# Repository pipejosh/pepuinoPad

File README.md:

# Pepuino Pad

This is the pepuino pad, a 9 by 9 midi launchpad, with per key rgb illumination (the brightness can only be set to 30% ish) the pepuino pad is a midi compatible launchpad to make music, this project, the shematics and the pcb are made in kicad, and the case and render are made in fusion 360 and it uses the custom made pepuino nano V1 as the main microcontroler (microcontroller based on a rp2040 chip)

###  Shematic
 
### pcb
 
### case
 
### render

## BOM

## Components (KIT)

| Item | Description | Quantity | Unit Price | Total Price | URL |
|-----|------------|----------|------------|-------------|-----|
| Blank keycaps | White | 90 | 0,13 | 11,81 | https://www.aliexpress.com/item/32842379355.html |
| Blank keycaps | Green | 20 | 0,19 | 3,77 | https://www.aliexpress.com/item/1005006116865547.html |
| Switches | Mechanical switches | 90 | 0,23 | 20,31 | https://www.aliexpress.com/item/1005009787231480.html |
| Diodes | SMD diodes | 100 | 0,03 | 3,08 | https://www.aliexpress.com/item/1005007160563285.html |
| M2 standoff | M2 standoff 5mm | 50 | 0,05 | 2,47 | https://www.aliexpress.com/item/1005006049595637.html |
| M2 screw | 5mm screw | 50 | 0,03 | 1,65 | https://www.aliexpress.com/item/1005005070119421.html |
| LED | SK6812 | 100 | 0,07 | 6,67 | https://www.aliexpress.com/item/1005005193716172.html |
| Roraty encoder | ec11 | 1 | 1,85 | 1,85 | https://www.aliexpress.com/item/1005007644083514.html |
| Taxes | AliExpress tax | — | — | 4,28 | — |

**Components Subtotal:** **55,89**

---

## PCB

| Item | Description | Price |
|-----|------------|-------|
| JLCPCB | Pepuino Pad PCB | 24,41 |
| JLCPCB Shipping | PCB shipping + taxes | 18,44 |

---

## Total

| Description | Amount |
|------------|--------|
| **Grand Total** | **98.74** |

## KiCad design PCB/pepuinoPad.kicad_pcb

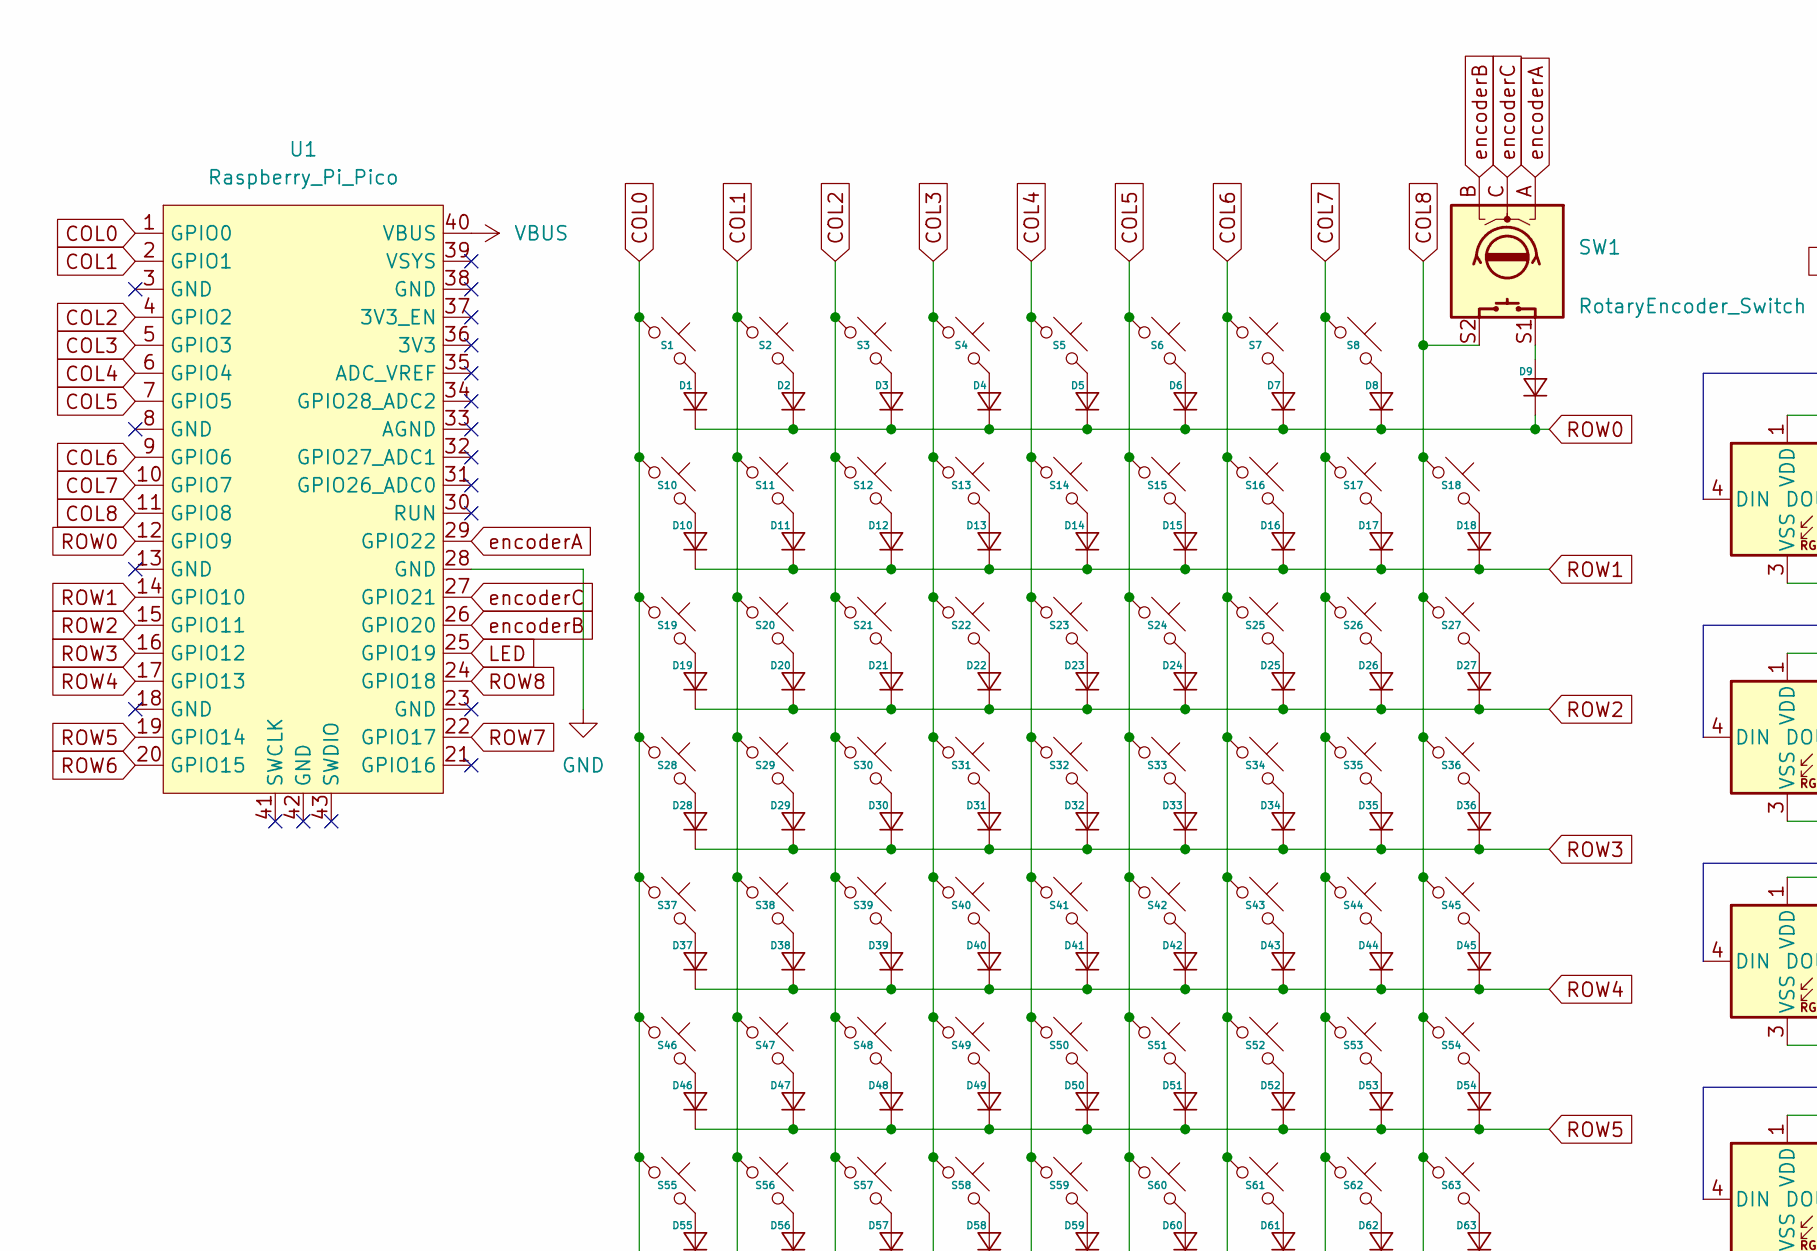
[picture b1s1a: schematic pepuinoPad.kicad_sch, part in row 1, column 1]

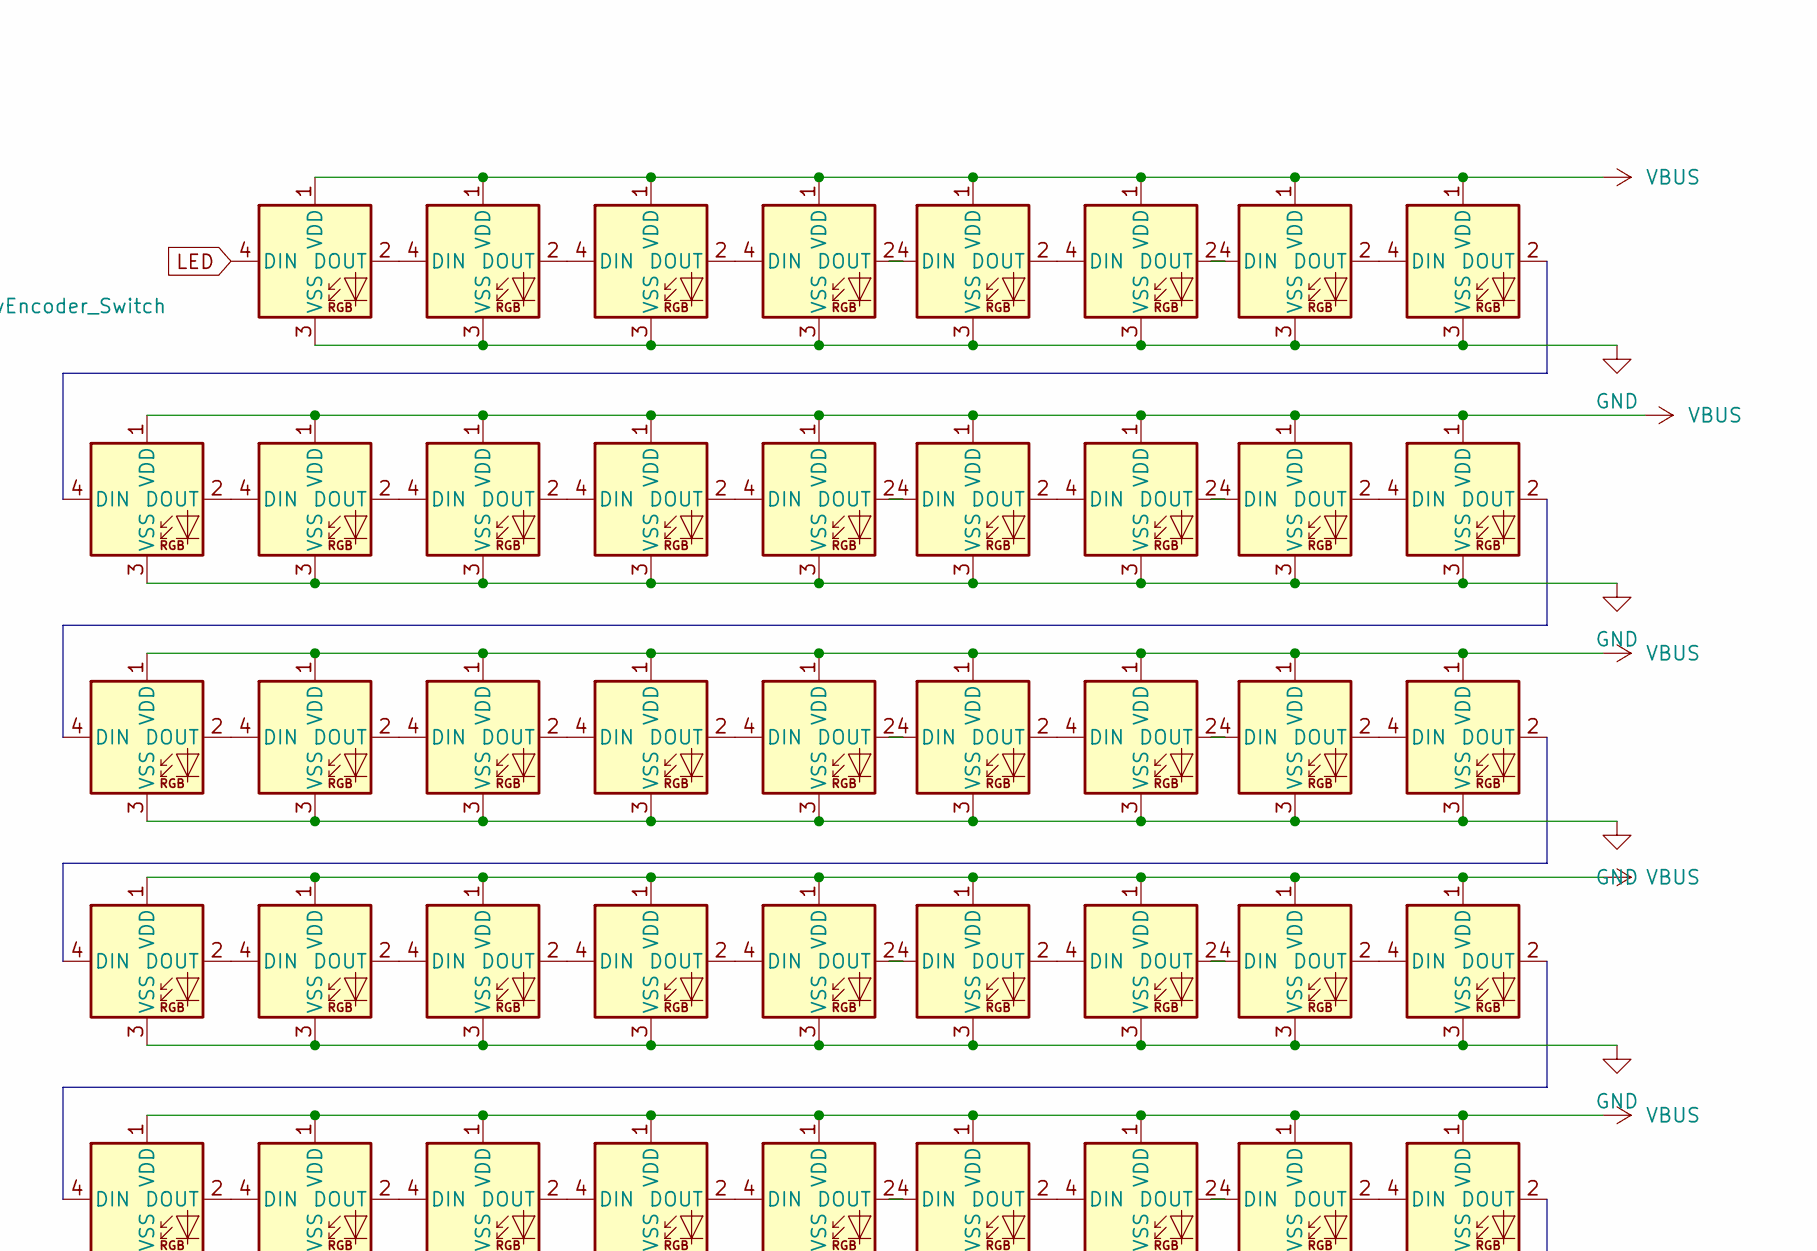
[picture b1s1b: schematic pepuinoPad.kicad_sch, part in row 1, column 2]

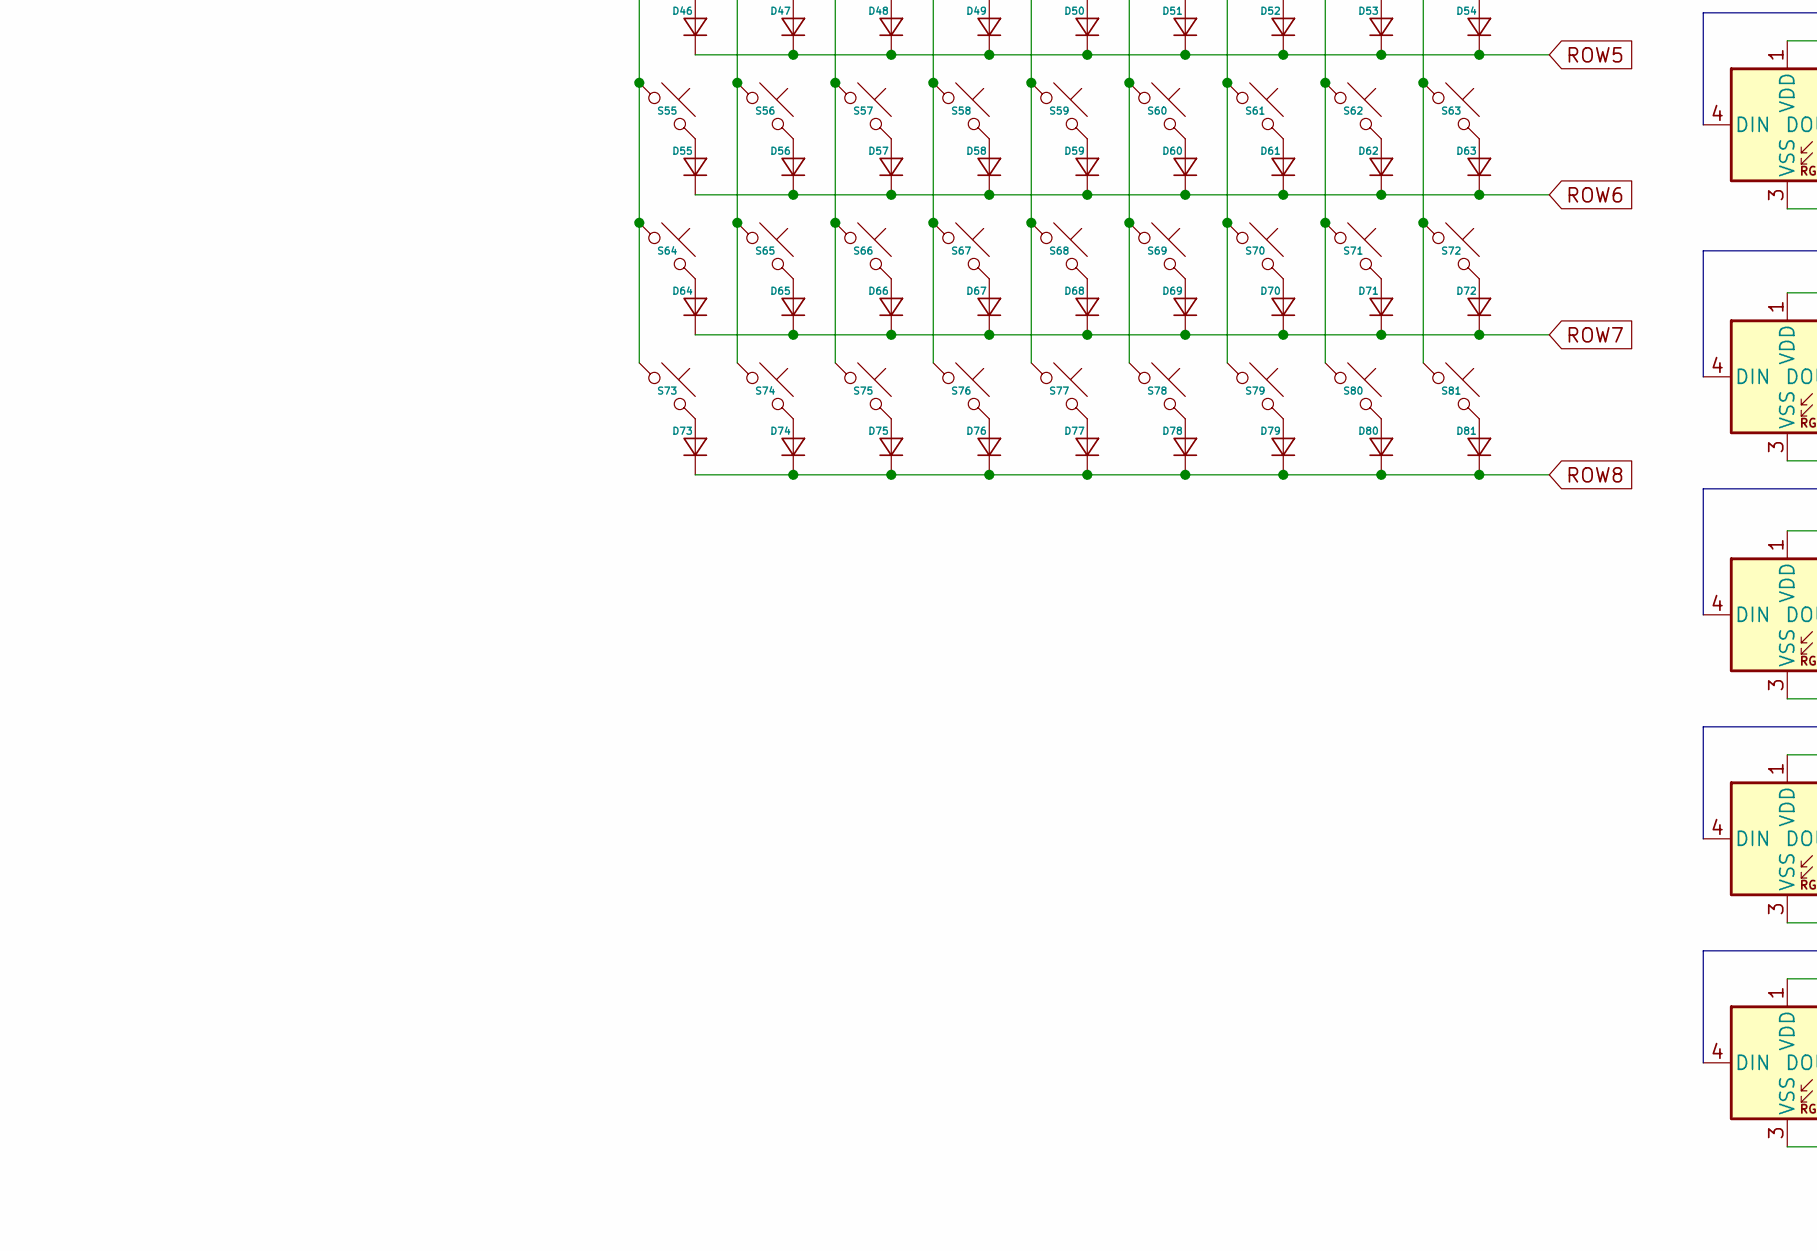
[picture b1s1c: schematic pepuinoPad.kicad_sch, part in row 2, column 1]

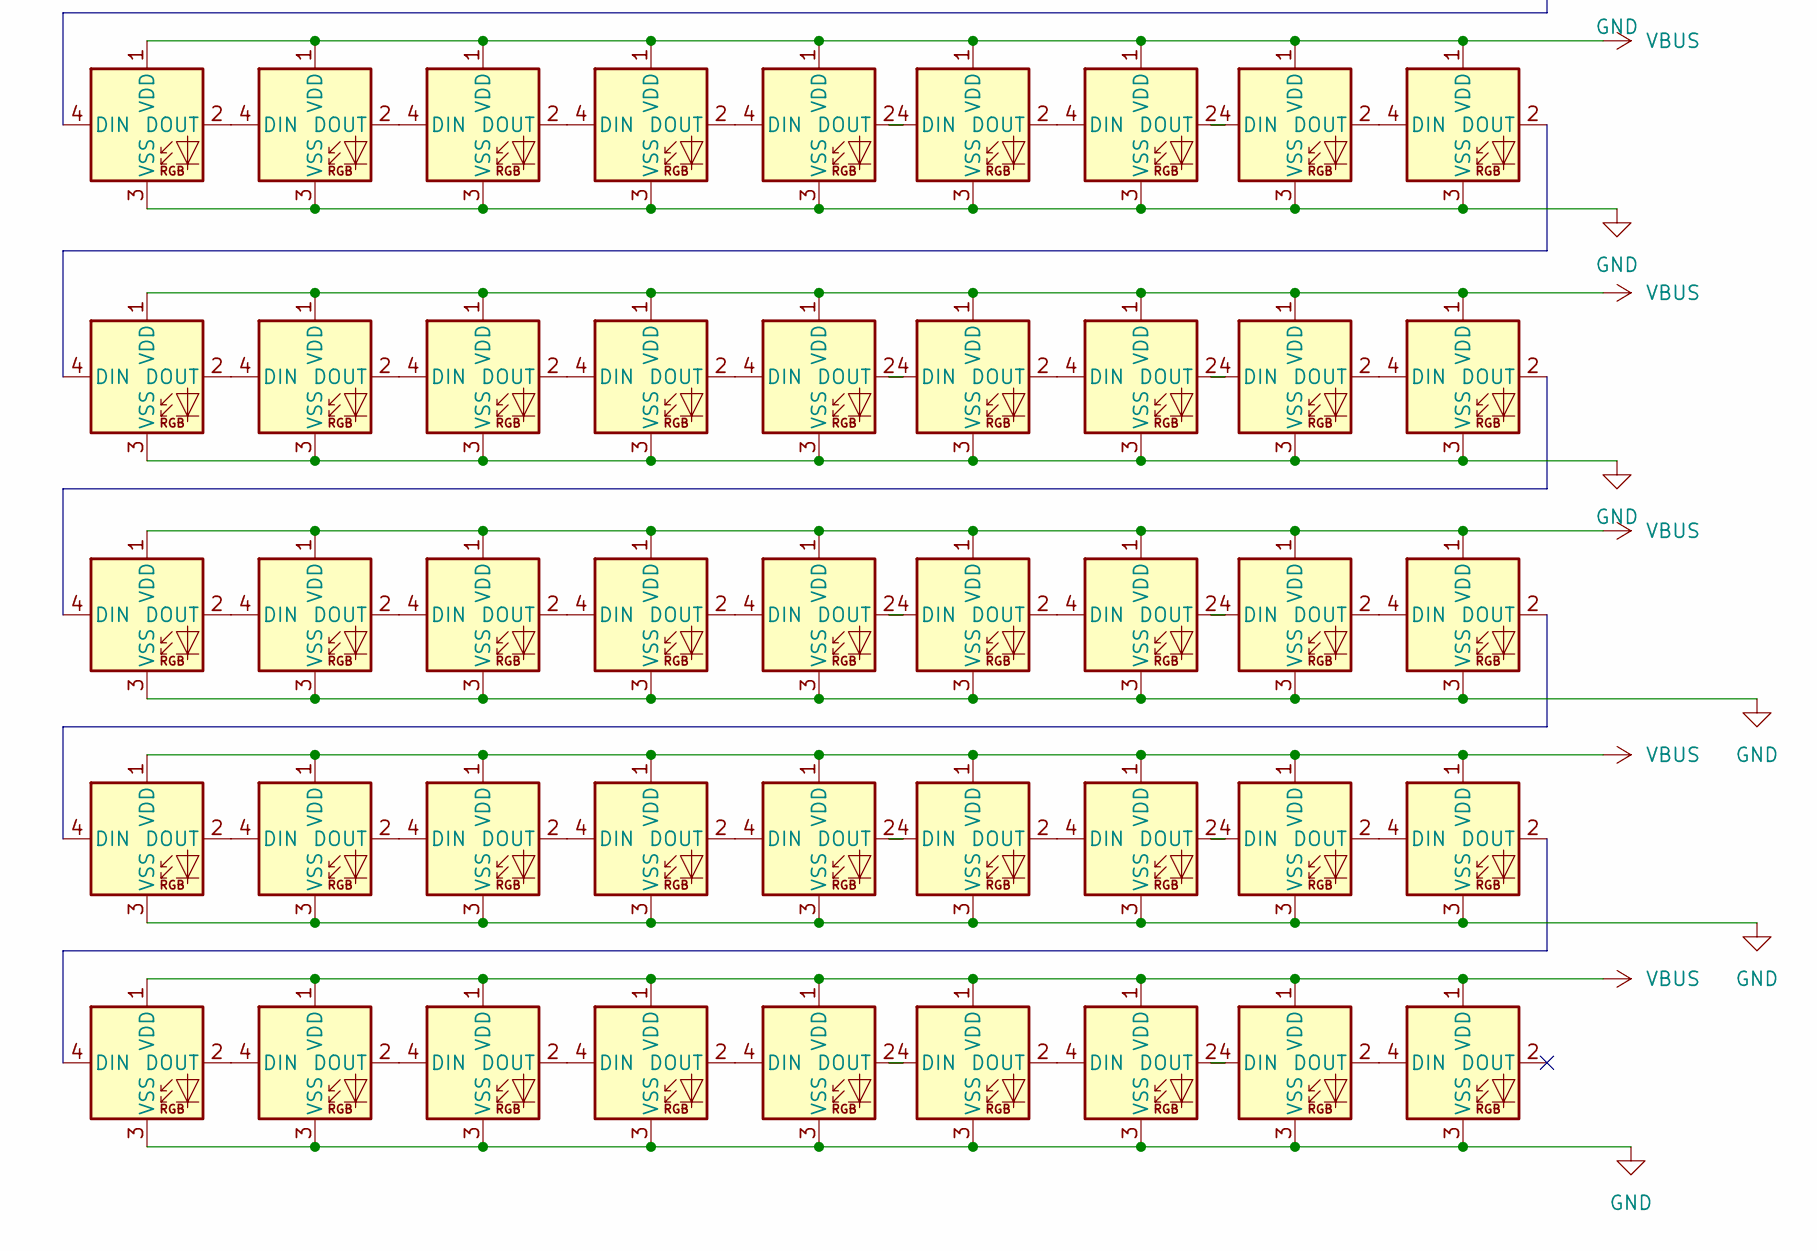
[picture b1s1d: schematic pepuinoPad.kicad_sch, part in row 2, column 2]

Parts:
D1, D2, D3, D4, D5, D6, D7, D8, D9, D10, D11, D12, D13, D14, D15, D16, D17, D18, D19, D20, D21, D22, D23, D24, D25, D26, D27, D28, D29, D30, D31, D32, D33, D34, D35, D36, D37, D38, D39, D40, D41, D42, D43, D44, D45, D46, D47, D48, D49, D50, D51, D52, D53, D54, D55, D56, D57, D58, D59, D60, D61, D62, D63, D64, D65, D66, D67, D68, D69, D70, D71, D72, D73, D74, D75, D76, D77, D78, D79, D80, D81: Diode_SOD-123
D83, D84, D85, D86, D87, D88, D89, D90, D91, D92, D93, D94, D95, D96, D97, D98, D99, D100, D101, D102, D103, D104, D105, D106, D107, D108, D109, D110, D111, D112, D113, D114, D115, D116, D117, D118, D119, D120, D121, D122, D123, D124, D125, D126, D127, D128, D129, D130, D131, D132, D133, D134, D135, D136, D137, D138, D139, D140, D141, D142, D143, D144, D145, D146, D147, D148, D149, D150, D151, D152, D153, D154, D155, D156, D157, D158, D159, D160, D161, D162: LED_SK6812MINI; YS-SK6812MINI-E; LCSC C5149201
S1, S2, S3, S4, S5, S6, S7, S8, S10, S11, S12, S13, S14, S15, S16, S17, S18, S19, S20, S21, S22, S23, S24, S25, S26, S27, S28, S29, S30, S31, S32, S33, S34, S35, S36, S37, S38, S39, S40, S41, S42, S43, S44, S45, S46, S47, S48, S49, S50, S51, S52, S53, S54, S55, S56, S57, S58, S59, S60, S61, S62, S63, S64, S65, S66, S67, S68, S69, S70, S71, S72, S73, S74, S75, S76, S77, S78, S79, S80, S81: MX_PCB_1.00u
SW1: RotaryEncoder_Switch; ROT_Alps_EC11E-Switch
U1: Raspberry_Pi_Pico

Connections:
COL0: S1.1, S10.1, S19.1, S28.1, S37.1, S46.1, S55.1, S64.1, S73.1, U1.1 (GPIO0)
COL1: S2.1, S11.1, S20.1, S29.1, S38.1, S47.1, S56.1, S65.1, S74.1, U1.2 (GPIO1)
COL2: S3.1, S12.1, S21.1, S30.1, S39.1, S48.1, S57.1, S66.1, S75.1, U1.4 (GPIO2)
COL3: S4.1, S13.1, S22.1, S31.1, S40.1, S49.1, S58.1, S67.1, S76.1, U1.5 (GPIO3)
COL4: S5.1, S14.1, S23.1, S32.1, S41.1, S50.1, S59.1, S68.1, S77.1, U1.6 (GPIO4)
COL5: S6.1, S15.1, S24.1, S33.1, S42.1, S51.1, S60.1, S69.1, S78.1, U1.7 (GPIO5)
COL6: S7.1, S16.1, S25.1, S34.1, S43.1, S52.1, S61.1, S70.1, S79.1, U1.9 (GPIO6)
COL7: S8.1, S17.1, S26.1, S35.1, S44.1, S53.1, S62.1, S71.1, S80.1, U1.10 (GPIO7)
COL8: S18.1, S27.1, S36.1, S45.1, S54.1, S63.1, S72.1, S81.1, SW1.S2, U1.11 (GPIO8)
GND: D83.3 (VSS), D84.3 (VSS), D85.3 (VSS), D86.3 (VSS), D87.3 (VSS), D88.3 (VSS), D89.3 (VSS), D90.3 (VSS), D91.3 (VSS), D92.3 (VSS), D93.3 (VSS), D94.3 (VSS), D95.3 (VSS), D96.3 (VSS), D97.3 (VSS), D98.3 (VSS), D99.3 (VSS), D100.3 (VSS), D101.3 (VSS), D102.3 (VSS), D103.3 (VSS), D104.3 (VSS), D105.3 (VSS), D106.3 (VSS), D107.3 (VSS), D108.3 (VSS), D109.3 (VSS), D110.3 (VSS), D111.3 (VSS), D112.3 (VSS), D113.3 (VSS), D114.3 (VSS), D115.3 (VSS), D116.3 (VSS), D117.3 (VSS), D118.3 (VSS), D119.3 (VSS), D120.3 (VSS), D121.3 (VSS), D122.3 (VSS), D123.3 (VSS), D124.3 (VSS), D125.3 (VSS), D126.3 (VSS), D127.3 (VSS), D128.3 (VSS), D129.3 (VSS), D130.3 (VSS), D131.3 (VSS), D132.3 (VSS), D133.3 (VSS), D134.3 (VSS), D135.3 (VSS), D136.3 (VSS), D137.3 (VSS), D138.3 (VSS), D139.3 (VSS), D140.3 (VSS), D141.3 (VSS), D142.3 (VSS), D143.3 (VSS), D144.3 (VSS), D145.3 (VSS), D146.3 (VSS), D147.3 (VSS), D148.3 (VSS), D149.3 (VSS), D150.3 (VSS), D151.3 (VSS), D152.3 (VSS), D153.3 (VSS), D154.3 (VSS), D155.3 (VSS), D156.3 (VSS), D157.3 (VSS), D158.3 (VSS), D159.3 (VSS), D160.3 (VSS), D161.3 (VSS), D162.3 (VSS), U1.28 (GND)
LED: D83.4 (DIN), U1.25 (GPIO19)
unnamed: D1.2 (A), S1.2
unnamed: D2.2 (A), S2.2
unnamed: D3.2 (A), S3.2
unnamed: D4.2 (A), S4.2
unnamed: D5.2 (A), S5.2
unnamed: D6.2 (A), S6.2
unnamed: D7.2 (A), S7.2
unnamed: D8.2 (A), S8.2
unnamed: D9.2 (A), SW1.S1
unnamed: D10.2 (A), S10.2
unnamed: D11.2 (A), S11.2
unnamed: D12.2 (A), S12.2
unnamed: D13.2 (A), S13.2
unnamed: D14.2 (A), S14.2
unnamed: D15.2 (A), S15.2
unnamed: D16.2 (A), S16.2
unnamed: D17.2 (A), S17.2
unnamed: D18.2 (A), S18.2
unnamed: D19.2 (A), S19.2
unnamed: D20.2 (A), S20.2
unnamed: D21.2 (A), S21.2
unnamed: D22.2 (A), S22.2
unnamed: D23.2 (A), S23.2
unnamed: D24.2 (A), S24.2
unnamed: D25.2 (A), S25.2
unnamed: D26.2 (A), S26.2
unnamed: D27.2 (A), S27.2
unnamed: D28.2 (A), S28.2
unnamed: D29.2 (A), S29.2
unnamed: D30.2 (A), S30.2
unnamed: D31.2 (A), S31.2
unnamed: D32.2 (A), S32.2
unnamed: D33.2 (A), S33.2
unnamed: D34.2 (A), S34.2
unnamed: D35.2 (A), S35.2
unnamed: D36.2 (A), S36.2
unnamed: D37.2 (A), S37.2
unnamed: D38.2 (A), S38.2
unnamed: D39.2 (A), S39.2
unnamed: D40.2 (A), S40.2
unnamed: D41.2 (A), S41.2
unnamed: D42.2 (A), S42.2
unnamed: D43.2 (A), S43.2
unnamed: D44.2 (A), S44.2
unnamed: D45.2 (A), S45.2
unnamed: D46.2 (A), S46.2
unnamed: D47.2 (A), S47.2
unnamed: D48.2 (A), S48.2
unnamed: D49.2 (A), S49.2
unnamed: D50.2 (A), S50.2
unnamed: D51.2 (A), S51.2
unnamed: D52.2 (A), S52.2
unnamed: D53.2 (A), S53.2
unnamed: D54.2 (A), S54.2
unnamed: D55.2 (A), S55.2
unnamed: D56.2 (A), S56.2
unnamed: D57.2 (A), S57.2
unnamed: D58.2 (A), S58.2
unnamed: D59.2 (A), S59.2
unnamed: D60.2 (A), S60.2
unnamed: D61.2 (A), S61.2
unnamed: D62.2 (A), S62.2
unnamed: D63.2 (A), S63.2
unnamed: D64.2 (A), S64.2
unnamed: D65.2 (A), S65.2
unnamed: D66.2 (A), S66.2
unnamed: D67.2 (A), S67.2
unnamed: D68.2 (A), S68.2
unnamed: D69.2 (A), S69.2
unnamed: D70.2 (A), S70.2
unnamed: D71.2 (A), S71.2
unnamed: D72.2 (A), S72.2
unnamed: D73.2 (A), S73.2
unnamed: D74.2 (A), S74.2
unnamed: D75.2 (A), S75.2
unnamed: D76.2 (A), S76.2
unnamed: D77.2 (A), S77.2
unnamed: D78.2 (A), S78.2
unnamed: D79.2 (A), S79.2
unnamed: D80.2 (A), S80.2
unnamed: D81.2 (A), S81.2
unnamed: D83.2 (DOUT), D84.4 (DIN)
unnamed: D84.2 (DOUT), D85.4 (DIN)
unnamed: D85.2 (DOUT), D86.4 (DIN)
unnamed: D86.2 (DOUT), D87.4 (DIN)
unnamed: D87.2 (DOUT), D88.4 (DIN)
unnamed: D88.2 (DOUT), D89.4 (DIN)
unnamed: D89.2 (DOUT), D90.4 (DIN)
unnamed: D90.2 (DOUT), D91.4 (DIN)
unnamed: D91.2 (DOUT), D92.4 (DIN)
unnamed: D92.2 (DOUT), D93.4 (DIN)
unnamed: D93.2 (DOUT), D94.4 (DIN)
unnamed: D94.2 (DOUT), D95.4 (DIN)
unnamed: D95.2 (DOUT), D96.4 (DIN)
unnamed: D96.2 (DOUT), D97.4 (DIN)
unnamed: D97.2 (DOUT), D98.4 (DIN)
unnamed: D98.2 (DOUT), D99.4 (DIN)
unnamed: D99.2 (DOUT), D100.4 (DIN)
unnamed: D100.2 (DOUT), D101.4 (DIN)
unnamed: D101.2 (DOUT), D102.4 (DIN)
unnamed: D102.2 (DOUT), D103.4 (DIN)
unnamed: D103.2 (DOUT), D104.4 (DIN)
unnamed: D104.2 (DOUT), D105.4 (DIN)
unnamed: D105.2 (DOUT), D106.4 (DIN)
unnamed: D106.2 (DOUT), D107.4 (DIN)
unnamed: D107.2 (DOUT), D108.4 (DIN)
unnamed: D108.2 (DOUT), D109.4 (DIN)
unnamed: D109.2 (DOUT), D110.4 (DIN)
unnamed: D110.2 (DOUT), D111.4 (DIN)
unnamed: D111.2 (DOUT), D112.4 (DIN)
unnamed: D112.2 (DOUT), D113.4 (DIN)
unnamed: D113.2 (DOUT), D114.4 (DIN)
unnamed: D114.2 (DOUT), D115.4 (DIN)
unnamed: D115.2 (DOUT), D116.4 (DIN)
unnamed: D116.2 (DOUT), D117.4 (DIN)
unnamed: D117.2 (DOUT), D118.4 (DIN)
unnamed: D118.2 (DOUT), D119.4 (DIN)
unnamed: D119.2 (DOUT), D120.4 (DIN)
unnamed: D120.2 (DOUT), D121.4 (DIN)
unnamed: D121.2 (DOUT), D122.4 (DIN)
unnamed: D122.2 (DOUT), D123.4 (DIN)
unnamed: D123.2 (DOUT), D124.4 (DIN)
unnamed: D124.2 (DOUT), D125.4 (DIN)
unnamed: D125.2 (DOUT), D126.4 (DIN)
unnamed: D126.2 (DOUT), D127.4 (DIN)
unnamed: D127.2 (DOUT), D128.4 (DIN)
unnamed: D128.2 (DOUT), D129.4 (DIN)
unnamed: D129.2 (DOUT), D130.4 (DIN)
unnamed: D130.2 (DOUT), D131.4 (DIN)
unnamed: D131.2 (DOUT), D132.4 (DIN)
unnamed: D132.2 (DOUT), D133.4 (DIN)
unnamed: D133.2 (DOUT), D134.4 (DIN)
unnamed: D134.2 (DOUT), D135.4 (DIN)
unnamed: D135.2 (DOUT), D136.4 (DIN)
unnamed: D136.2 (DOUT), D137.4 (DIN)
unnamed: D137.2 (DOUT), D138.4 (DIN)
unnamed: D138.2 (DOUT), D139.4 (DIN)
unnamed: D139.2 (DOUT), D140.4 (DIN)
unnamed: D140.2 (DOUT), D141.4 (DIN)
unnamed: D141.2 (DOUT), D142.4 (DIN)
unnamed: D142.2 (DOUT), D143.4 (DIN)
unnamed: D143.2 (DOUT), D144.4 (DIN)
unnamed: D144.2 (DOUT), D145.4 (DIN)
unnamed: D145.2 (DOUT), D146.4 (DIN)
unnamed: D146.2 (DOUT), D147.4 (DIN)
unnamed: D147.2 (DOUT), D148.4 (DIN)
unnamed: D148.2 (DOUT), D149.4 (DIN)
unnamed: D149.2 (DOUT), D150.4 (DIN)
unnamed: D150.2 (DOUT), D151.4 (DIN)
unnamed: D151.2 (DOUT), D152.4 (DIN)
unnamed: D152.2 (DOUT), D153.4 (DIN)
unnamed: D153.2 (DOUT), D154.4 (DIN)
unnamed: D154.2 (DOUT), D155.4 (DIN)
unnamed: D155.2 (DOUT), D156.4 (DIN)
unnamed: D156.2 (DOUT), D157.4 (DIN)
unnamed: D157.2 (DOUT), D158.4 (DIN)
unnamed: D158.2 (DOUT), D159.4 (DIN)
unnamed: D159.2 (DOUT), D160.4 (DIN)
unnamed: D160.2 (DOUT), D161.4 (DIN)
unnamed: D161.2 (DOUT), D162.4 (DIN)
ROW0: D1.1 (K), D2.1 (K), D3.1 (K), D4.1 (K), D5.1 (K), D6.1 (K), D7.1 (K), D8.1 (K), D9.1 (K), U1.12 (GPIO9)
ROW1: D10.1 (K), D11.1 (K), D12.1 (K), D13.1 (K), D14.1 (K), D15.1 (K), D16.1 (K), D17.1 (K), D18.1 (K), U1.14 (GPIO10)
ROW2: D19.1 (K), D20.1 (K), D21.1 (K), D22.1 (K), D23.1 (K), D24.1 (K), D25.1 (K), D26.1 (K), D27.1 (K), U1.15 (GPIO11)
ROW3: D28.1 (K), D29.1 (K), D30.1 (K), D31.1 (K), D32.1 (K), D33.1 (K), D34.1 (K), D35.1 (K), D36.1 (K), U1.16 (GPIO12)
ROW4: D37.1 (K), D38.1 (K), D39.1 (K), D40.1 (K), D41.1 (K), D42.1 (K), D43.1 (K), D44.1 (K), D45.1 (K), U1.17 (GPIO13)
ROW5: D46.1 (K), D47.1 (K), D48.1 (K), D49.1 (K), D50.1 (K), D51.1 (K), D52.1 (K), D53.1 (K), D54.1 (K), U1.19 (GPIO14)
ROW6: D55.1 (K), D56.1 (K), D57.1 (K), D58.1 (K), D59.1 (K), D60.1 (K), D61.1 (K), D62.1 (K), D63.1 (K), U1.20 (GPIO15)
ROW7: D64.1 (K), D65.1 (K), D66.1 (K), D67.1 (K), D68.1 (K), D69.1 (K), D70.1 (K), D71.1 (K), D72.1 (K), U1.22 (GPIO17)
ROW8: D73.1 (K), D74.1 (K), D75.1 (K), D76.1 (K), D77.1 (K), D78.1 (K), D79.1 (K), D80.1 (K), D81.1 (K), U1.24 (GPIO18)
VBUS: D83.1 (VDD), D84.1 (VDD), D85.1 (VDD), D86.1 (VDD), D87.1 (VDD), D88.1 (VDD), D89.1 (VDD), D90.1 (VDD), D91.1 (VDD), D92.1 (VDD), D93.1 (VDD), D94.1 (VDD), D95.1 (VDD), D96.1 (VDD), D97.1 (VDD), D98.1 (VDD), D99.1 (VDD), D100.1 (VDD), D101.1 (VDD), D102.1 (VDD), D103.1 (VDD), D104.1 (VDD), D105.1 (VDD), D106.1 (VDD), D107.1 (VDD), D108.1 (VDD), D109.1 (VDD), D110.1 (VDD), D111.1 (VDD), D112.1 (VDD), D113.1 (VDD), D114.1 (VDD), D115.1 (VDD), D116.1 (VDD), D117.1 (VDD), D118.1 (VDD), D119.1 (VDD), D120.1 (VDD), D121.1 (VDD), D122.1 (VDD), D123.1 (VDD), D124.1 (VDD), D125.1 (VDD), D126.1 (VDD), D127.1 (VDD), D128.1 (VDD), D129.1 (VDD), D130.1 (VDD), D131.1 (VDD), D132.1 (VDD), D133.1 (VDD), D134.1 (VDD), D135.1 (VDD), D136.1 (VDD), D137.1 (VDD), D138.1 (VDD), D139.1 (VDD), D140.1 (VDD), D141.1 (VDD), D142.1 (VDD), D143.1 (VDD), D144.1 (VDD), D145.1 (VDD), D146.1 (VDD), D147.1 (VDD), D148.1 (VDD), D149.1 (VDD), D150.1 (VDD), D151.1 (VDD), D152.1 (VDD), D153.1 (VDD), D154.1 (VDD), D155.1 (VDD), D156.1 (VDD), D157.1 (VDD), D158.1 (VDD), D159.1 (VDD), D160.1 (VDD), D161.1 (VDD), D162.1 (VDD), U1.40 (VBUS)
encoderA: SW1.A, U1.29 (GPIO22)
encoderB: SW1.B, U1.26 (GPIO20)
encoderC: SW1.C, U1.27 (GPIO21)

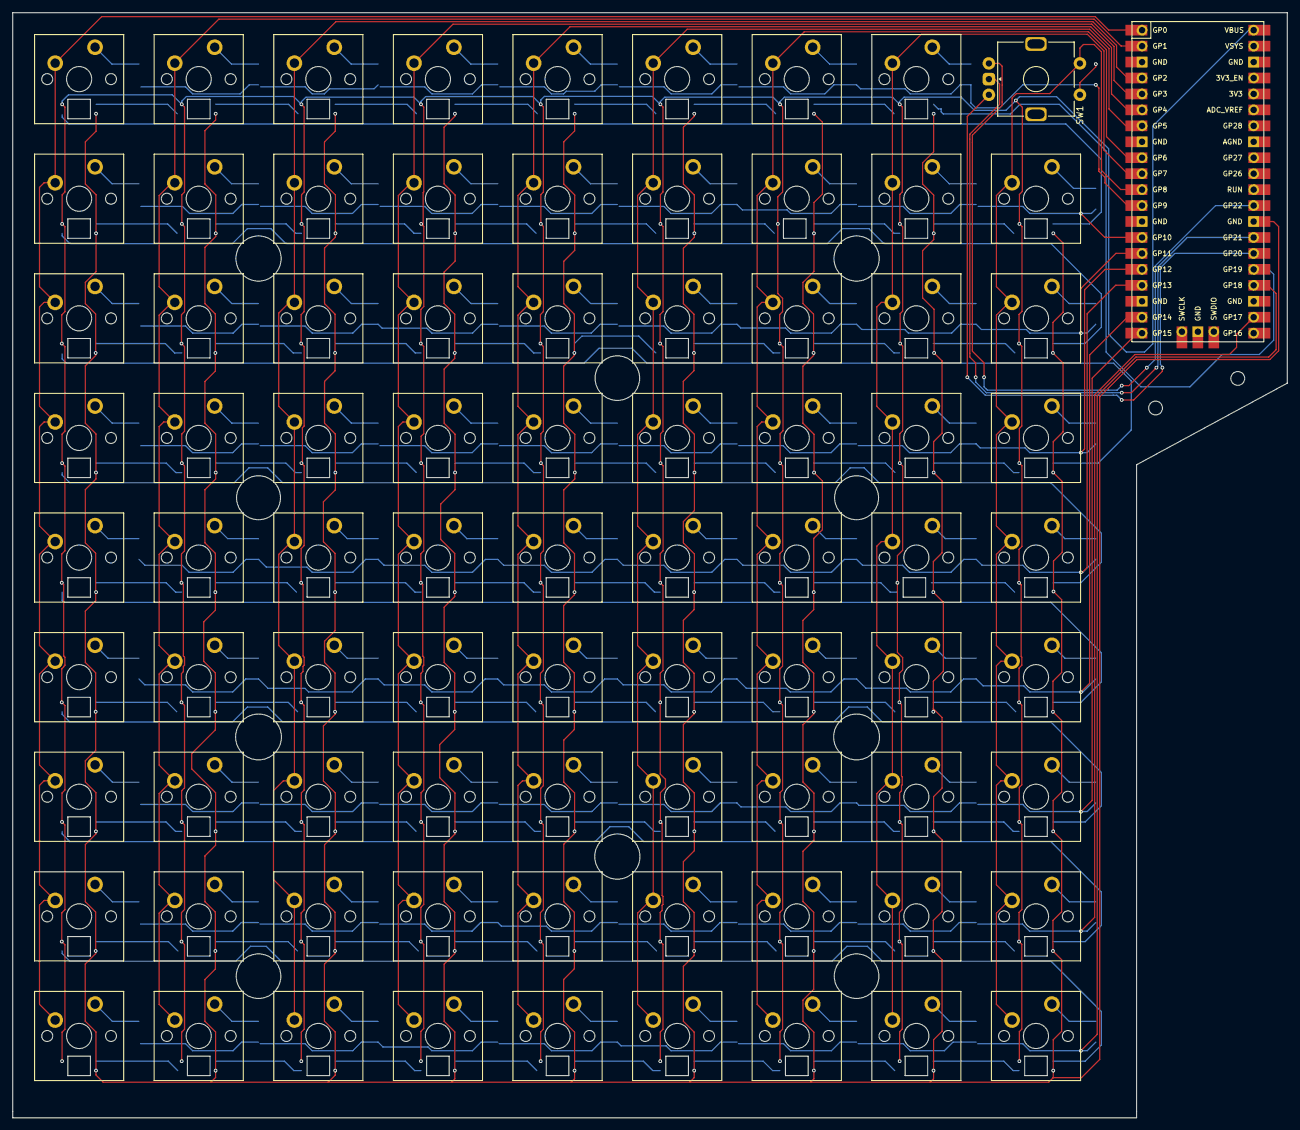
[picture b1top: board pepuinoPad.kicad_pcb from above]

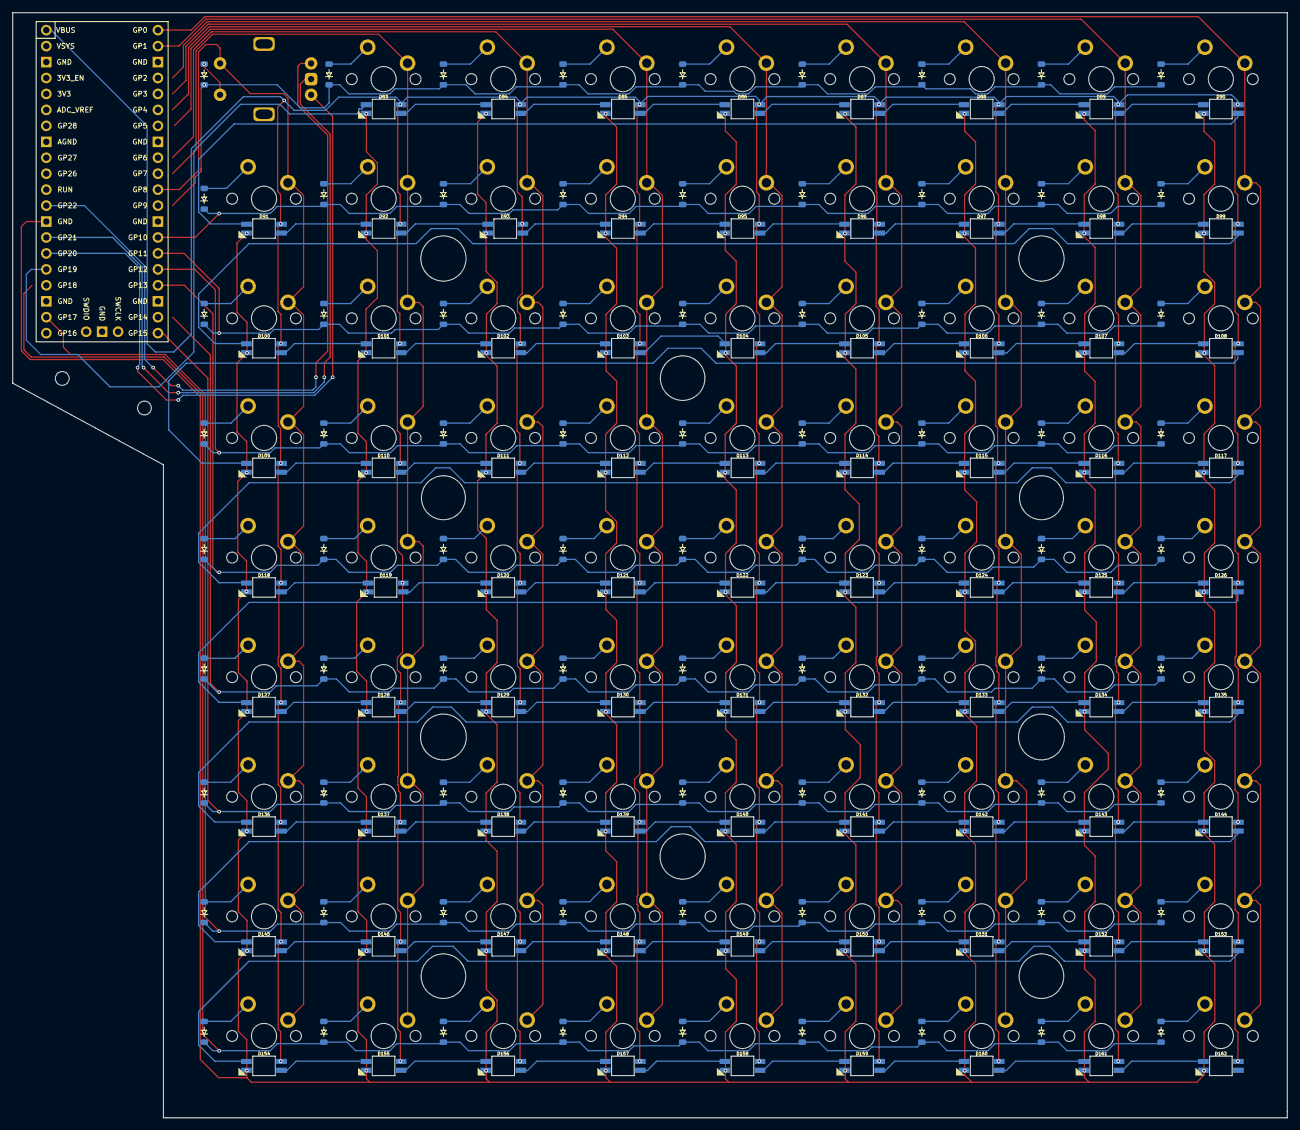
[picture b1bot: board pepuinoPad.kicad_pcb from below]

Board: 2 copper layers, 203.0 x 176.0 mm, 245 parts (161 on the bottom side), 184 nets.

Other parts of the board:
H11, H12: MountingHole; MountingHole_2.2mm_M2

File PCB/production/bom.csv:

Designator,Footprint,Quantity,Value,LCSC Part #
"D1, D10, D11, D12, D13, D14, D15, D16, D17, D18, D19, D2, D20, D21, D22, D23, D24, D25, D26, D27, D28, D29, D3, D30, D31, D32, D33, D34, D35, D36, D37, D38, D39, D4, D40, D41, D42, D43, D44, D45, D46, D47, D48, D49, D5, D50, D51, D52, D53, D54, D55, D56, D57, D58, D59, D6, D60, D61, D62, D63, D64, D65, D66, D67, D68, D69, D7, D70, D71, D72, D73, D74, D75, D76, D77, D78, D79, D8, D80, D81, D9",Diode_SOD-123,81,~,
"D100, D101, D102, D103, D104, D105, D106, D107, D108, D109, D110, D111, D112, D113, D114, D115, D116, D117, D118, D119, D120, D121, D122, D123, D124, D125, D126, D127, D128, D129, D130, D131, D132, D133, D134, D135, D136, D137, D138, D139, D140, D141, D142, D143, D144, D145, D146, D147, D148, D149, D150, D151, D152, D153, D154, D155, D156, D157, D158, D159, D160, D161, D162, D82, D83, D84, D85, D86, D87, D88, D89, D90, D91, D92, D93, D94, D95, D96, D97, D98, D99",LED_SK6812MINI,81,LED_SK6812MINI,C5149201
"S1, S10, S11, S12, S13, S14, S15, S16, S17, S18, S19, S2, S20, S21, S22, S23, S24, S25, S26, S27, S28, S29, S3, S30, S31, S32, S33, S34, S35, S36, S37, S38, S39, S4, S40, S41, S42, S43, S44, S45, S46, S47, S48, S49, S5, S50, S51, S52, S53, S54, S55, S56, S57, S58, S59, S6, S60, S61, S62, S63, S64, S65, S66, S67, S68, S69, S7, S70, S71, S72, S73, S74, S75, S76, S77, S78, S79, S8, S80, S81, S9",MX_PCB_1.00u,81,~,
U1,Raspberry_Pi_Pico,1,Raspberry_Pi_Pico,

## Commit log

2026-01-05 add other files
2026-01-05 add remaining files
2026-01-05 add updated BOM
2026-01-05 add firmware (untested)
2026-01-06 Update README with BOM image and formatting
2026-02-06 update pictes / case / pcb / BOM
2026-02-23 add roatry encododer + pepuino nano + update readme and img
2026-02-23 Update images in README.md
    Removed duplicate render3 image and adjusted render2 image formatting.
2026-03-09 Revise component prices and grand total in README
    Updated component list and adjusted totals.
2026-03-10 Fix Roraty encoder quantity and update subtotal
    Corrected quantity for Roraty encoder and updated subtotal.
2026-03-10 Fix component prices and add microcontroller details
    Updated the README.md to correct component prices and clarify microcontroller details.
